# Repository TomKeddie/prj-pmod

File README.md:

# prj-pmod

A collection of BSD licensed hardware designs for the PMOD form factor.

MIT licensed - see https://github.com/TomKeddie/prj-pmod/blob/master/LICENSE

## tom-prj-pmod

This is a PMOD module with a SAMD21 cpu on it to make it easy to add an ARM cpu to an fpga project.

Hardware : https://github.com/TomKeddie/prj-pmod/tree/master/hardware/pmod-samd21

Bootloader : https://github.com/TomKeddie/prj-pmod/tree/master/software/pmod-samd21

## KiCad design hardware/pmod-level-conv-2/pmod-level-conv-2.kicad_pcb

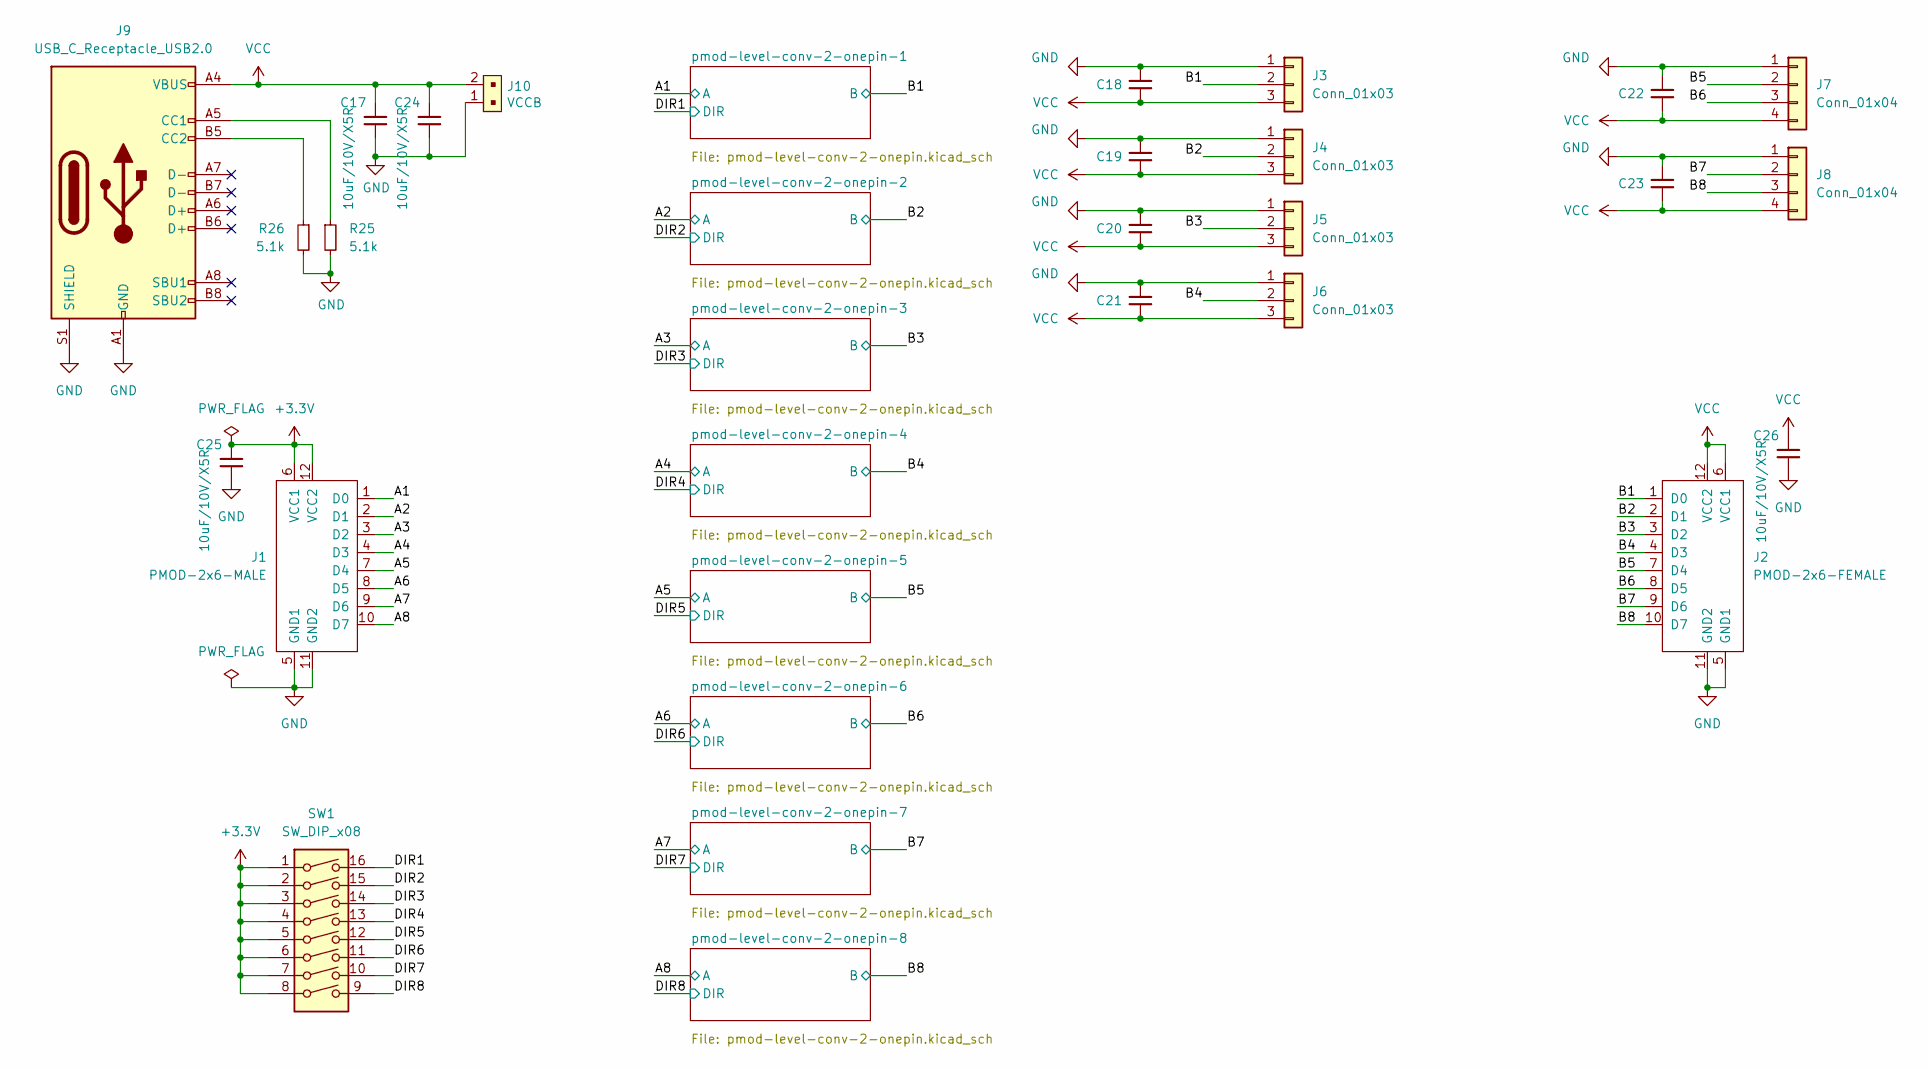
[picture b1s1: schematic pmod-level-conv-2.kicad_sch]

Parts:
C17, C18, C19, C20, C21, C22, C23, C24, C25, C26: 10uF/10V/X5R; C_0603_1608Metric; MFGPN CL10A106KP8NNNC; LCSC C19702
J1: PMOD-2x6-MALE; PMOD_2X6_PTH_RA_PLUG; LCSC DNP
J2: PMOD-2x6-FEMALE; PMOD_2X6_PTH_RA_SOCKET; LCSC DNP
J3, J4, J5, J6: Conn_01x03; CONN_ZH_3P_HORIZ_C722679; LCSC C722679
J7, J8: Conn_01x04; CONN_ZH_4P_HORIZ_C5248024; LCSC C5248024
J9: USB_C_Receptacle_USB2.0; USB_C_Receptacle_LCSC_C165948; LCSC C165948
J10: VCCB; CONN_ZH_2P_HORIZ_C265329; LCSC C265329
R25, R26: 5.1k; R_0402_1005Metric; MFGPN 0402WGF5101TCE; LCSC C25905
SW1: SW_DIP_x08; DIP-16_W7.62mm_Socket_LongPads; LCSC DNP

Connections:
+3.3V: C25.1, J1.6 (VCC1), J1.12 (VCC2), SW1.1, SW1.2, SW1.3, SW1.4, SW1.5, SW1.6, SW1.7, SW1.8; also elsewhere on the board
/A1: J1.1 (D0); also elsewhere on the board
/A2: J1.2 (D1); also elsewhere on the board
/A3: J1.3 (D2); also elsewhere on the board
/A4: J1.4 (D3); also elsewhere on the board
/A5: J1.7 (D4); also elsewhere on the board
/A6: J1.8 (D5); also elsewhere on the board
/A7: J1.9 (D6); also elsewhere on the board
/A8: J1.10 (D7); also elsewhere on the board
/B1: J2.1 (D0), J3.2; also elsewhere on the board
/B2: J2.2 (D1), J4.2; also elsewhere on the board
/B3: J2.3 (D2), J5.2; also elsewhere on the board
/B4: J2.4 (D3), J6.2; also elsewhere on the board
/B5: J2.7 (D4), J7.2; also elsewhere on the board
/B6: J2.8 (D5), J7.3; also elsewhere on the board
/B7: J2.9 (D6), J8.2; also elsewhere on the board
/B8: J2.10 (D7), J8.3; also elsewhere on the board
/DIR1: SW1.16; also elsewhere on the board
/DIR2: SW1.15; also elsewhere on the board
/DIR3: SW1.14; also elsewhere on the board
/DIR4: SW1.13; also elsewhere on the board
/DIR5: SW1.12; also elsewhere on the board
/DIR6: SW1.11; also elsewhere on the board
/DIR7: SW1.10; also elsewhere on the board
/DIR8: SW1.9; also elsewhere on the board
GND: C17.2, C18.1, C19.1, C20.1, C21.1, C22.1, C23.1, C24.2, C25.2, C26.2, J1.5 (GND1), J1.11 (GND2), J2.5 (GND1), J2.11 (GND2), J3.1, J4.1, J5.1, J6.1, J7.1, J8.1, J9.A1 (GND), J9.A12 (GND), J9.B1 (GND), J9.B12 (GND), J9.S1 (SHIELD), J10.1, R25.2, R26.2; also elsewhere on the board
unnamed: J9.A5 (CC1), R25.1
unnamed: J9.B5 (CC2), R26.1
VCC: C17.1, C18.2, C19.2, C20.2, C21.2, C22.2, C23.2, C24.1, C26.1, J2.6 (VCC1), J2.12 (VCC2), J3.3, J4.3, J5.3, J6.3, J7.4, J8.4, J9.A4 (VBUS), J9.A9 (VBUS), J9.B4 (VBUS), J9.B9 (VBUS), J10.2; also elsewhere on the board

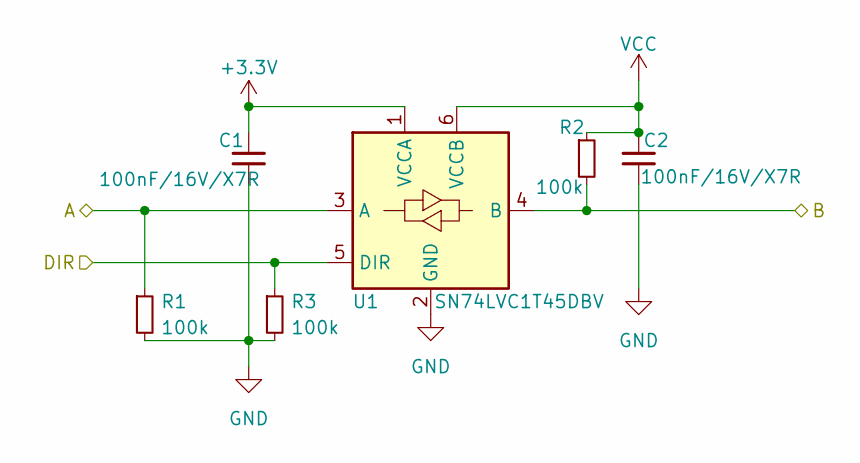
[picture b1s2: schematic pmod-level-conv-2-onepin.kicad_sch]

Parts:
C1, C2: 100nF/16V/X7R; C_0402_1005Metric; MFGPN CL05B104KO5NNNC; LCSC C1525
R1, R2, R3: 100k; R_0402_1005Metric; MFGPN 0402WGF1003TCE; LCSC C25741
U1: SN74LVC1T45DBV; SOT-23-6; LCSC C7843

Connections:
+3.3V: C1.1, U1.1 (VCCA); also elsewhere on the board
/A1: R1.1, U1.3 (A); also elsewhere on the board
/B1: R2.2, U1.4 (B); also elsewhere on the board
/DIR1: R3.1, U1.5 (DIR); also elsewhere on the board
GND: C1.2, C2.2, R1.2, R3.2, U1.2 (GND); also elsewhere on the board
VCC: C2.1, R2.1, U1.6 (VCCB); also elsewhere on the board

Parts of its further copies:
C3, C4, C5, C6, C7, C8, C9, C10, C11, C12, C13, C14, C15, C16: 100nF/16V/X7R; C_0402_1005Metric; MFGPN CL05B104KO5NNNC; LCSC C1525
R4, R5, R6, R7, R8, R9, R10, R11, R12, R13, R14, R15, R16, R17, R18, R19, R20, R21, R22, R23, R24: 100k; R_0402_1005Metric; MFGPN 0402WGF1003TCE; LCSC C25741
U2, U3, U4, U5, U6, U7, U8: SN74LVC1T45DBV; SOT-23-6; LCSC C7843

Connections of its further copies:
+3.3V: C3.1, C5.1, C7.1, C9.1, C11.1, C13.1, C15.1, U2.1 (VCCA), U3.1 (VCCA), U4.1 (VCCA), U5.1 (VCCA), U6.1 (VCCA), U7.1 (VCCA), U8.1 (VCCA); also elsewhere on the board
/A2: R5.1, U2.3 (A); also elsewhere on the board
/A3: R8.1, U3.3 (A); also elsewhere on the board
/A4: R11.1, U4.3 (A); also elsewhere on the board
/A5: R14.1, U5.3 (A); also elsewhere on the board
/A6: R17.1, U6.3 (A); also elsewhere on the board
/A7: R20.1, U7.3 (A); also elsewhere on the board
/A8: R23.1, U8.3 (A); also elsewhere on the board
/B2: R4.2, U2.4 (B); also elsewhere on the board
/B3: R7.2, U3.4 (B); also elsewhere on the board
/B4: R10.2, U4.4 (B); also elsewhere on the board
/B5: R13.2, U5.4 (B); also elsewhere on the board
/B6: R16.2, U6.4 (B); also elsewhere on the board
/B7: R19.2, U7.4 (B); also elsewhere on the board
/B8: R22.2, U8.4 (B); also elsewhere on the board
/DIR2: R6.1, U2.5 (DIR); also elsewhere on the board
/DIR3: R9.1, U3.5 (DIR); also elsewhere on the board
/DIR4: R12.1, U4.5 (DIR); also elsewhere on the board
/DIR5: R15.1, U5.5 (DIR); also elsewhere on the board
/DIR6: R18.1, U6.5 (DIR); also elsewhere on the board
/DIR7: R21.1, U7.5 (DIR); also elsewhere on the board
/DIR8: R24.1, U8.5 (DIR); also elsewhere on the board
GND: C3.2, C4.2, C5.2, C6.2, C7.2, C8.2, C9.2, C10.2, C11.2, C12.2, C13.2, C14.2, C15.2, C16.2, R5.2, R6.2, R8.2, R9.2, R11.2, R12.2, R14.2, R15.2, R17.2, R18.2, R20.2, R21.2, R23.2, R24.2, U2.2 (GND), U3.2 (GND), U4.2 (GND), U5.2 (GND), U6.2 (GND), U7.2 (GND), U8.2 (GND); also elsewhere on the board
VCC: C4.1, C6.1, C8.1, C10.1, C12.1, C14.1, C16.1, R4.1, R7.1, R10.1, R13.1, R16.1, R19.1, R22.1, U2.6 (VCCB), U3.6 (VCCB), U4.6 (VCCB), U5.6 (VCCB), U6.6 (VCCB), U7.6 (VCCB), U8.6 (VCCB); also elsewhere on the board

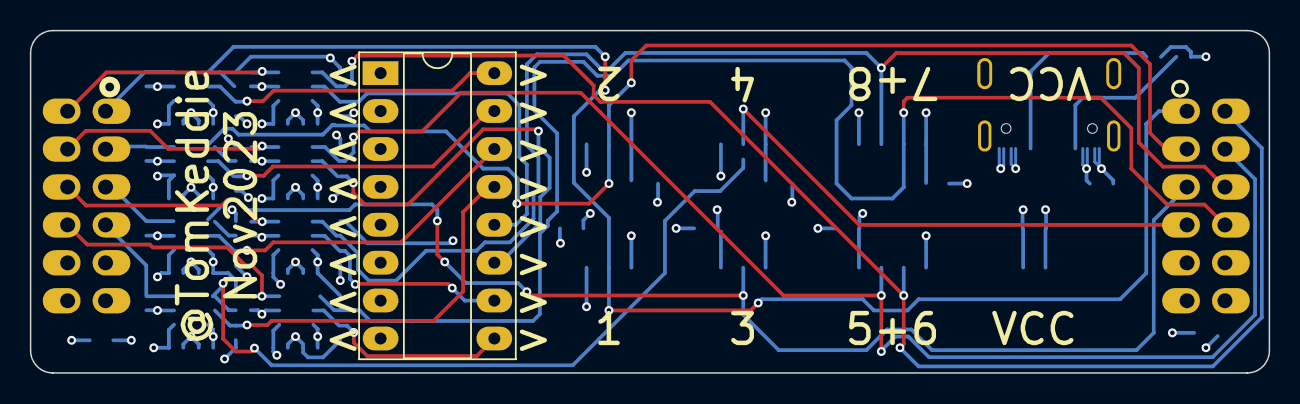
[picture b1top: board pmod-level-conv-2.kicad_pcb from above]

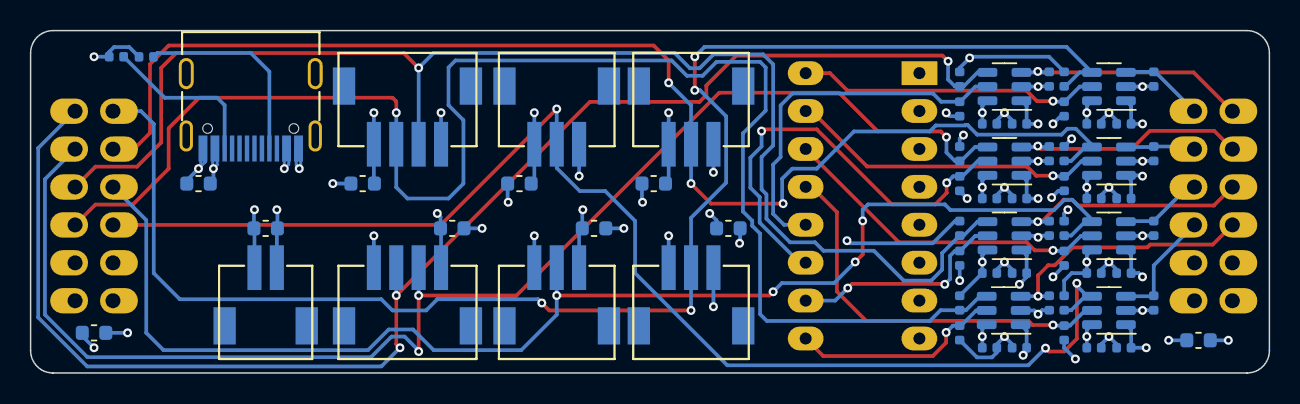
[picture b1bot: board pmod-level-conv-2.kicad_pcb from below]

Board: 4 copper layers, 83.0 x 22.9 mm, 71 parts (68 on the bottom side), 29 nets.

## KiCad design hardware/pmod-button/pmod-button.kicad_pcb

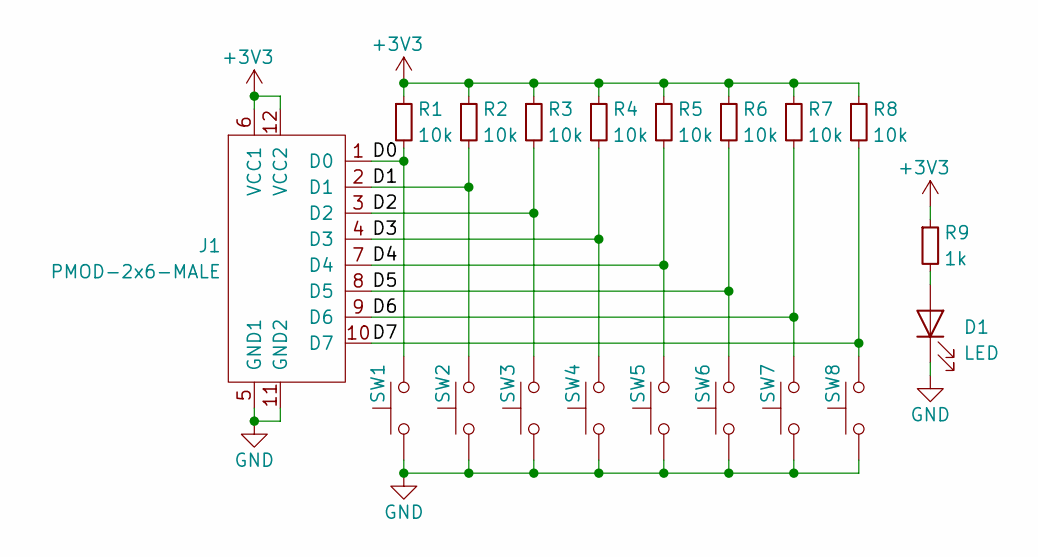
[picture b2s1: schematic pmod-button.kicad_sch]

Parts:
D1: LED; LED_0805_2012Metric_Pad1.15x1.40mm_HandSolder
J1: PMOD-2x6-MALE; PMOD_2X6_PTH_RA_PLUG
R1, R2, R3, R4, R5, R6, R7, R8: 10k; C_0805_2012Metric_Pad1.15x1.40mm_HandSolder
R9: 1k; C_0805_2012Metric_Pad1.15x1.40mm_HandSolder
SW1, SW2, SW3, SW4, SW5, SW6, SW7, SW8: Switch_SW_Push; SW_Push_1P1T_NO_CK_PTS125Sx43PSMTR

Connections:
+3V3: J1.6 (VCC1), J1.12 (VCC2), R1.1, R2.1, R3.1, R4.1, R5.1, R6.1, R7.1, R8.1, R9.1
/D0: J1.1 (D0), R1.2, SW1.2
/D1: J1.2 (D1), R2.2, SW2.2
/D2: J1.3 (D2), R3.2, SW3.2
/D3: J1.4 (D3), R4.2, SW4.2
/D4: J1.7 (D4), R5.2, SW5.2
/D5: J1.8 (D5), R6.2, SW6.2
/D6: J1.9 (D6), R7.2, SW7.2
/D7: J1.10 (D7), R8.2, SW8.2
GND: D1.1 (K), J1.5 (GND1), J1.11 (GND2), SW1.1, SW2.1, SW3.1, SW4.1, SW5.1, SW6.1, SW7.1, SW8.1
unnamed: D1.2 (A), R9.2

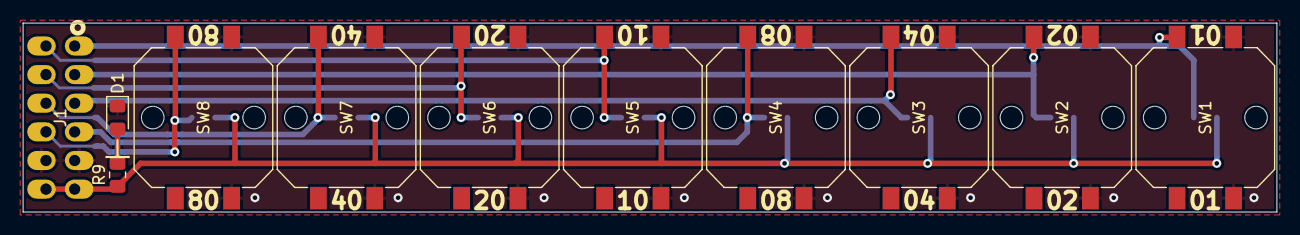
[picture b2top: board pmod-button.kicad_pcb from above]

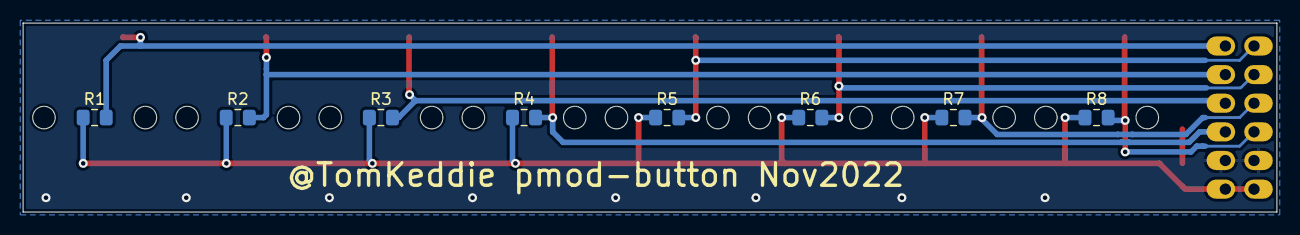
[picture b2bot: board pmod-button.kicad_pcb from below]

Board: 2 copper layers, 111.3 x 16.8 mm, 19 parts (8 on the bottom side), 11 nets.

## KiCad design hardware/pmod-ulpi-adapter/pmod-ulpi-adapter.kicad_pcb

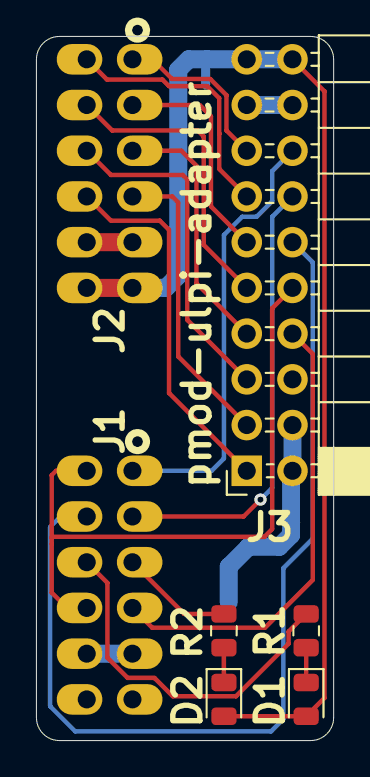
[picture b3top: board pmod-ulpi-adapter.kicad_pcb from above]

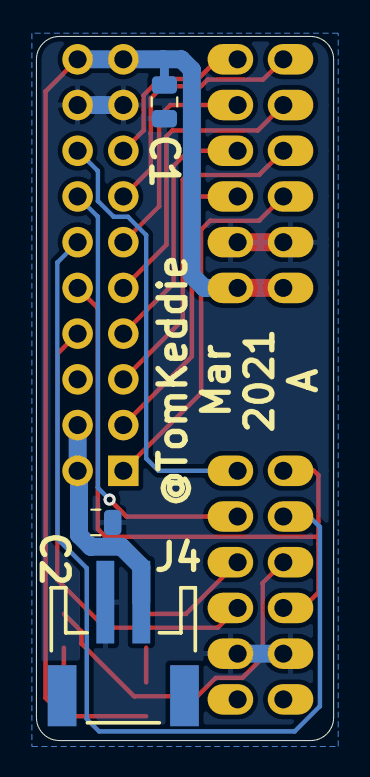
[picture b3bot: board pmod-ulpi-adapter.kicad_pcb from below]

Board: 2 copper layers, 16.5 x 39.1 mm, 10 parts (3 on the bottom side), 20 nets.

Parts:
C1, C2: 10uF/10V; C_0805_2012Metric
D1, D2: LED; LED_0805_2012Metric
J1, J2: PMOD-2x6-MALE; PMOD_2X6_PTH_RA_PLUG
J3: ULPI; PinSocket_2x10_P2.54mm_Horizontal
J4: Conn_01x02; JST-2-SMD
R1, R2: 1k; R_0805_2012Metric

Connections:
+3V3: C1.2, D1.2, D2.2, J2.6, J2.12, J3.19, J3.20
+5V: C2.2, J3.2, J3.4, J4.1
/BLUE: J1.9, R1.2
/CLKOUT: J1.7, J1.10, J3.10
/DATA0: J2.10, J3.1
/DATA1: J2.4, J3.3
/DATA2: J2.9, J3.5
/DATA3: J2.3, J3.7
/DATA4: J2.8, J3.9
/DATA5: J2.2, J3.11
/DATA6: J2.7, J3.13
/DATA7: J2.1, J3.15
/DIR: J1.8, J3.12
/NXT: J1.2, J3.14
/RESET: J1.4, J3.8
/STP: J1.1, J3.16
/YELLOW: J1.3, R2.1
GND: C1.1, C2.1, J1.5, J1.11, J2.5, J2.11, J3.17, J3.18, J4.2
unnamed: D1.1, R1.1
unnamed: D2.1, R2.2

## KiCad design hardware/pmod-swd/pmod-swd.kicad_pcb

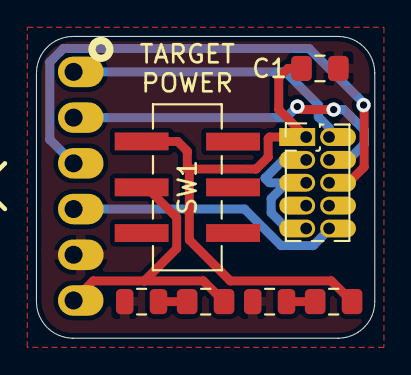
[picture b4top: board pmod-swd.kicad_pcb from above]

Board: 2 copper layers, 18.8 x 16.8 mm, 8 parts (0 on the bottom side), 9 nets.

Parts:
C1: 10uF/6.3V; C_0805_2012Metric_Pad1.15x1.40mm_HandSolder
D1, D2: LED; C_0805_2012Metric_Pad1.15x1.40mm_HandSolder
J1: PMOD; PMOD_1X6_PTH_RA_PLUG
J2: SWD; PinHeader_2x05_P1.27mm_Vertical
R1, R2: 1k; R_0805_2012Metric
SW1: SW_DPDT_x2; SW_DPDT_SMD

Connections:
!RESET: J1.4, J2.10
+3V3: D1.2, J1.6, SW1.2
GND: C1.2, J1.5, J2.3, J2.5, J2.9, R1.2, R2.2
unnamed: D1.1, R1.1
unnamed: D2.1, R2.1
SWDCLK: J1.2, J2.4
SWDIO: J1.1, J2.2
SWO: J1.3, J2.6
VCC: C1.1, D2.2, J2.1, SW1.3

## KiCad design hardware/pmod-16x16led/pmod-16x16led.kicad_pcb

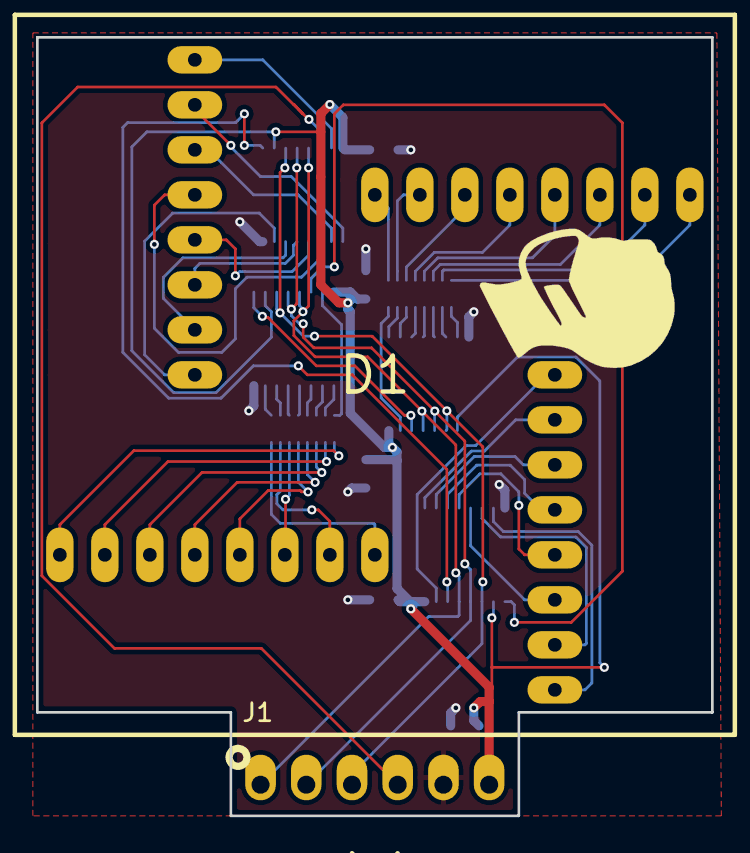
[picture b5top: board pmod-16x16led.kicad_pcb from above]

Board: 2 copper layers, 37.5 x 43.2 mm, 13 parts (0 on the bottom side), 57 nets.

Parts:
C1: 10uF/6.3V; C_0603_1608Metric
C2, C3, C4, C5: 0.1uF/6.3V; C_0603_1608Metric
D1: SLD161616DRA2B
J1: Conn_01x06; PMOD_1X6_PTH_RA_PLUG
RP1, RP2: 330R; R_PACK8_CAT16J8
U1, U2, U3, U4: 74HC595; SSOP-16_3.9x4.9mm_P0.635mm

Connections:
+3V3: C1.1, C2.1, C3.1, C4.1, C5.1, J1.6, U1.10, U1.16, U2.10, U2.16, U3.10, U3.16, U4.10, U4.16
/!OE: J1.1, U1.13, U2.13, U3.13, U4.13
/A1: D1.25, U1.15
/A2: D1.26, U1.1
/A3: D1.27, U1.2
/A4: D1.28, U1.3
/A5: D1.29, U1.4
/A6: D1.30, U1.5
/A7: D1.31, U1.6
/A8: D1.32, U1.7
/A9: D1.16, U2.15
/A10: D1.15, U2.1
/A11: D1.14, U2.2
/A12: D1.13, U2.3
/A13: D1.12, U2.4
/A14: D1.11, U2.5
/A15: D1.10, U2.6
/A16: D1.9, U2.7
/C1: D1.1, RP1.9
/C2: D1.2, RP1.10
/C3: D1.3, RP1.11
/C4: D1.4, RP1.12
/C5: D1.5, RP1.13
/C6: D1.6, RP1.14
/C7: D1.7, RP1.15
/C8: D1.8, RP1.16
/C9: D1.24, RP2.9
/C10: D1.23, RP2.10
/C11: D1.22, RP2.11
/C12: D1.21, RP2.12
/C13: D1.20, RP2.13
/C14: D1.19, RP2.14
/C15: D1.18, RP2.15
/C16: D1.17, RP2.16
/CLK: J1.3, U1.11, U2.11, U3.11, U4.11
/DATA: J1.4, U1.14
/DATA-A8: U1.9, U2.14
/DATA-A16: U2.9, U3.14
/DATA-C8: U3.9, U4.14
/RCLK: J1.2, U1.12, U2.12, U3.12, U4.12
GND: C1.2, C2.2, C3.2, C4.2, C5.2, J1.5, U1.8, U2.8, U3.8, U4.8
unnamed: RP1.1, U3.7
unnamed: RP1.2, U3.6
unnamed: RP1.3, U3.5
unnamed: RP1.4, U3.4
unnamed: RP1.5, U3.3
unnamed: RP1.6, U3.2
unnamed: RP1.7, U3.1
unnamed: RP1.8, U3.15
unnamed: RP2.1, U4.7
unnamed: RP2.2, U4.6
unnamed: RP2.3, U4.5
unnamed: RP2.4, U4.4
unnamed: RP2.5, U4.3
unnamed: RP2.6, U4.2
unnamed: RP2.7, U4.1
unnamed: RP2.8, U4.15

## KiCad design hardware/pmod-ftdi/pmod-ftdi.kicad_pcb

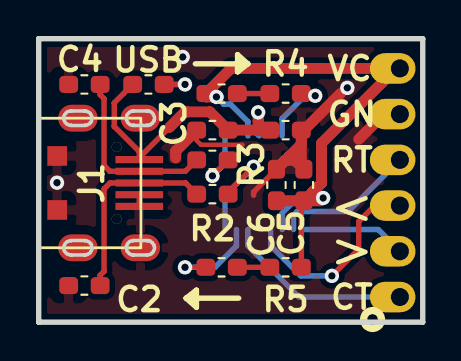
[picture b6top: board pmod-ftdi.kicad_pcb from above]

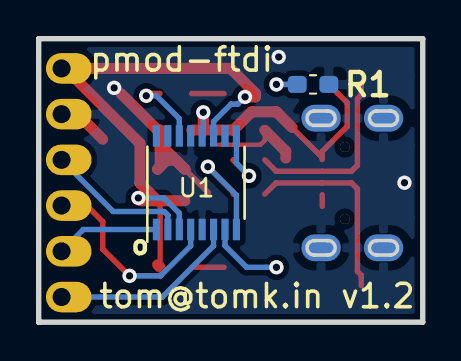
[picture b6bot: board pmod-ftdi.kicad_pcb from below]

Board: 2 copper layers, 21.3 x 15.7 mm, 17 parts (2 on the bottom side), 16 nets.

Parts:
C1, C5: 4.7uF; C_0603_1608Metric_Pad1.05x0.95mm_HandSolder
C2, C4: 47pF; C_0603_1608Metric_Pad1.05x0.95mm_HandSolder
C3, C6: 0.1uF; C_0603_1608Metric_Pad1.05x0.95mm_HandSolder
D1: VBUS; R_0603_1608Metric_Pad1.05x0.95mm_HandSolder
D2: TX; R_0603_1608Metric_Pad1.05x0.95mm_HandSolder
D3: RX; R_0603_1608Metric_Pad1.05x0.95mm_HandSolder
J1: USB_B_Micro; USB_MICRO_TAOBAO_SMD_PTH
J2: PMOD-1x6-MALE; PMOD_1X6_PTH_RA_PLUG
R1, R4, R5: 1k; R_0603_1608Metric_Pad1.05x0.95mm_HandSolder
R2, R3: 27R; R_0603_1608Metric_Pad1.05x0.95mm_HandSolder
U1: FT230XS-R; SSOP-16_3.9x4.9mm_P0.635mm

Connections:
/CBUS1: R4.1, U1.14
/CBUS2: D3.1, U1.7
/CTS: J2.1, U1.6
/D_N: R3.2, U1.9
/D_P: R2.1, U1.8
/RTS: J2.4, U1.2
/RXD: J2.3, U1.4
/RXLED: D3.2, R5.1
/TXD: J2.2, U1.1
/TXLED: D2.1, R4.2
/UD_N: C4.1, J1.2, R3.1
/UD_P: C2.1, J1.3, R2.2
/VBUSLED: D1.1, R1.2
GND: C1.2, C2.2, C3.2, C4.2, C5.2, C6.2, J1.4, J1.5, J1.6, J2.5, R1.1, U1.5, U1.13
VBUS: C1.1, C3.1, D1.2, J1.1, U1.12
VCCIO: C5.1, C6.1, D2.2, J2.6, R5.2, U1.3, U1.11

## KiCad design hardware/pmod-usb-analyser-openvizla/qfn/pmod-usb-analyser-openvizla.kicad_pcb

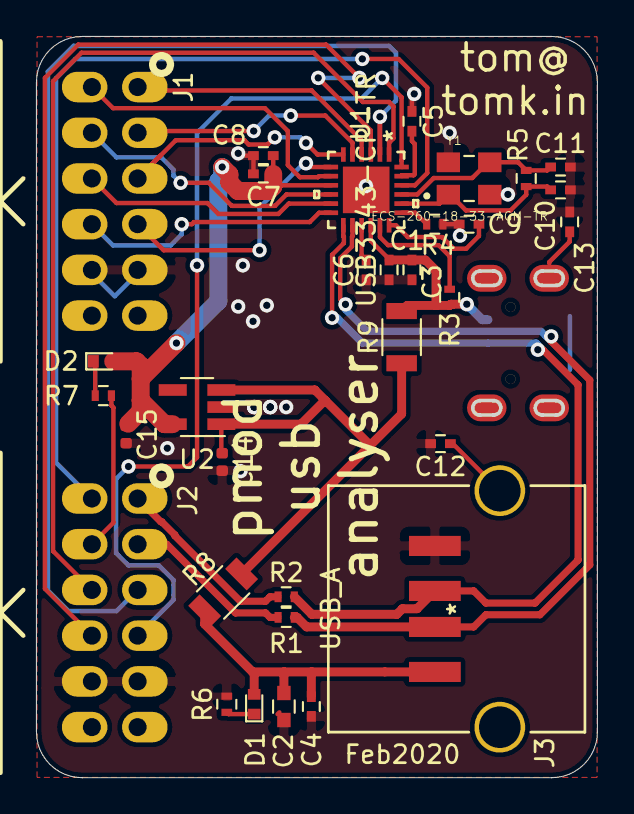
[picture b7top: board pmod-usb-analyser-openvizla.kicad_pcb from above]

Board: 2 copper layers, 31.0 x 41.0 mm, 33 parts (1 on the bottom side), 34 nets.

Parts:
C1, C3, C7, C9: 0.1uF; C_0402
C2: 10uF; C_0603
C4, C5, C6, C8: 1uF; C_0402
C10, C11: 18pF; C_0402
C12, C13: 0.1uF/6.3V; C_0402
C14, C15: 1uF; C_0402_1005Metric
D1, D2: LED; LED_0402
J1, J2: PMOD-2x6-MALE; PMOD_2X6_PTH_RA_PLUG
J3: USB_A; 87583-2010BLF
J4: USB_B_Micro; USB_MICRO_TAOBAO_SMD_PTH
R1, R2: 1k; R_0402
R3: 10k; R_0402
R4: 8k06/1%; R_0402
R5: 1M; R_0402
R6: 1K; R_0402
R7: 330R; R_0402
R8, R9: R; R_1206
U1: USB3343-CP-TR
U2: AP2112K-3.3; SOT-23-5_HandSoldering
Y1: ECS-260-18-33-AGM-TR; XTAL_ECS-260-18-33-AGM-TR

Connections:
+3V3: C7.1, C8.1, C15.1, D2.2, U1.9, U2.5
/CLKOUT: J2.3, U1.2
/DATA0: J1.1, U1.4
/DATA1: J1.2, U1.5
/DATA2: J1.3, U1.6
/DATA3: J1.4, U1.7
/DATA4: J1.7, U1.8
/DATA5: J1.8, U1.10
/DATA6: J1.9, U1.11
/DATA7: J1.10, U1.12
/DIR: J2.9, U1.1
/ID: C9.1, U1.18
/J3_SHIELD: C12.1, J3.5
/J4_SHIELD: C13.1, J4.6
/NXT: J2.10, U1.3
/RBIAS: R4.2, U1.19
/RESETB: J2.7, U1.22
/STP: J2.4, U1.24
/USB_TAP_DP: J2.1, R2.1
/USER_LED: J2.8, R7.2
/VBUS: C2.1, C4.1, D1.2, J3.1, R8.1
/VBUS_SENSE: R3.1, U1.17
/VDD18: C5.1, U1.23
/VDD33: C6.1, U1.15
/X0: C10.1, R5.1, U1.20, Y1.1
/XI: C11.1, R5.2, U1.21, Y1.3
GND: C1.2, C2.2, C3.2, C4.2, C5.2, C6.2, C7.2, C8.2, C9.2, C10.2, C11.2, C12.2, C13.2, C14.2, C15.2, J1.5, J1.11, J2.5, J2.11, J3.4, J4.5, R4.1, R6.2, U1.25, U2.2, Y1.2, Y1.4
unnamed: D1.1, R6.1
unnamed: D2.1, R7.1
unnamed: J2.2, R1.1
USB_DN: J3.2, J4.2, R1.2, U1.14
USB_DP: J3.3, J4.3, R2.2, U1.13
VBUS1: C14.1, R8.2, R9.1, U2.1, U2.3
VBUS2: C1.1, C3.1, J4.1, R3.2, R9.2, U1.16

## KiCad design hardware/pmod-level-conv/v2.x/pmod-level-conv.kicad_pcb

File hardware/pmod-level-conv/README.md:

# PMOD Level Converter

Converts up in voltage only (within specs of TXB0108).  Would be trivial to flip/reverse the connectors and hack the board to convert down.

Status : TSSOP v1.0 tested and working. TSOP v1.2 tested, changed only side of header pads. VQFN v1.3 untested.

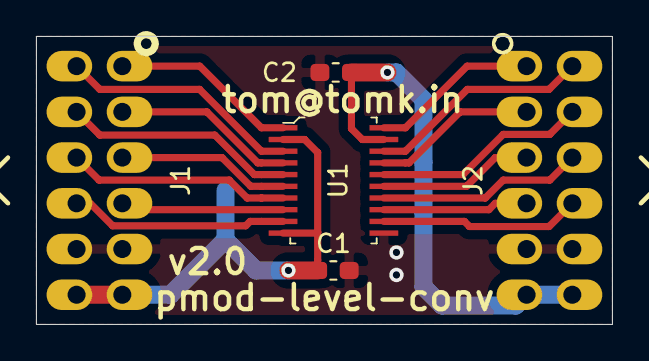
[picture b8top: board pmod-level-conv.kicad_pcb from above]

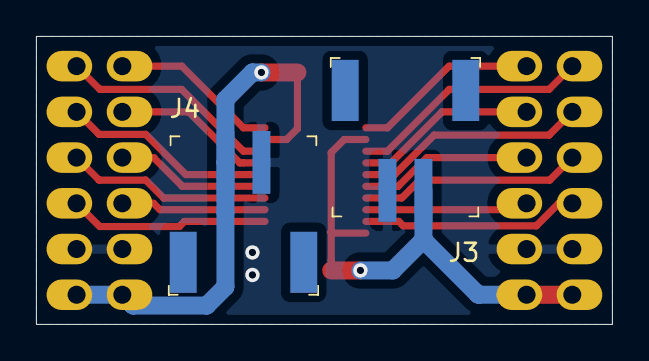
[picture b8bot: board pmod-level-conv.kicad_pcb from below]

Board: 2 copper layers, 32.0 x 16.0 mm, 7 parts (2 on the bottom side), 19 nets.

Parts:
C1, C2: 0.1uF/10V; C_0603_1608Metric_Pad1.05x0.95mm_HandSolder
J1: PMOD-2x6-MALE; PMOD_2X6_PTH_RA_PLUG
J2: PMOD-2x6-FEMALE; PMOD_2X6_PTH_RA_SOCKET
J3: VCCA; PinHeader_2x1mm_P2mm_SMD_RA
J4: VCCB; PinHeader_2x1mm_P2mm_SMD_RA
U1: TXB0108PWR; TSSOP-20_W4.4mm

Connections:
/A1: J1.1, U1.1
/A2: J1.7, U1.3
/A3: J1.2, U1.4
/A4: J1.8, U1.5
/A5: J1.3, U1.6
/A6: J1.9, U1.7
/A7: J1.4, U1.8
/A8: J1.10, U1.9
/B1: J2.1, U1.20
/B2: J2.7, U1.18
/B3: J2.2, U1.17
/B4: J2.8, U1.16
/B5: J2.3, U1.15
/B6: J2.9, U1.14
/B7: J2.4, U1.13
/B8: J2.10, U1.12
/VCCA: C1.1, J1.6, J1.12, J3.2, U1.2, U1.10
/VCCB: C2.1, J2.6, J2.12, J4.2, U1.19
GND: C1.2, C2.2, J1.5, J1.11, J2.5, J2.11, J3.1, J4.1, U1.11

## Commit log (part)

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2018-05-27 PMOD USB RAW for tinyfpga bootloader - rev 1.0 as sent to oshpark
2018-06-20 Added README
2018-06-20 Add oshpark link
2018-06-20 Added images of USB PMOD
2018-06-20 Added BOM for usb pmod
2018-06-20 Updated usb README to add octopart
2018-06-20 Add image for usb raw pmod
2018-06-20 Add image to USB readme
2018-06-20 Update README to show image
2018-06-20 Fix typo in README
2018-06-24 pmod level converter added (v1.0 as sent to oshpark)
2018-07-26 Update level conv pcb to rev 1.1 - fix smd pad sizes for pmod connectors
2018-07-27 Eight LED PMOD as submitted to OSH Park
2018-08-06 Added APA102 PMOD board
2018-08-06 APA102 PMD as submitted to Oshpark (minor silk fixups)
2018-08-13 pmod-level-conv : fixed NC OE
2018-10-28 Added VQFN version of pmod level converter
2018-10-28 Added eagle samd5x5 schematic
2018-10-30 First pass at kicad schematic for samd21 pmod
2018-10-31 Add kicad backups to gitignore
2018-10-31 First pass at routing of samd21 pmod, power yet to be done
2018-10-31 PCB fully routed with DRC errors ignored - oshpark doesn't like the slots in the usb connector - need to check FET pinout
2018-11-26 pcb as submitted to oshpark
2018-11-26 Added pmod-samd21 openocd config
2018-11-26 Add samd bootloader from Arduino for pmod-samd21
2018-11-26 Add sam_ba build for pmod-samd21 with led on B23
2018-11-26 Fix path to sam_ba binary
2018-12-05 pmod-samd21 : Fixed edge cuts for panelisation with plated slots
2018-12-07 pmod-samd21 - added missing usb C resistors - generated gerbers relative to aux origin
2018-12-07 pmod-samd21 : rename to create usb-c variant
2018-12-07 pmod-samd : clone usbc variant to make microusb variant
2018-12-09 SAMD21 PMOD microusb version
2018-12-09 pmod-samd21 : add missing gerbers for usbu variant
2018-12-09 pmod-samd21 : Move usbu gerbers to separate folder
2018-12-31 Updated led pmod
2019-01-16 Added pcb for micro usb samd21 pmod
2019-01-16 pmod-samd21 : routed and ready for fab
2019-03-20 Add ibom for pmod-samd21-usbu
2019-03-20 Create LICENSE
2019-03-20 pmod-samd21-usbu-pth : as sent to fab
2019-03-20 gerber-usbu-pth : add missing drill file
2019-03-20 Update README.md
    Add Arduino digital and analog pin numbers
2019-03-20 Update README.md
    Add arduino aliases
2019-03-21 Update README.md
    Add notes on power supply.
2019-04-25 pmod-samd21 : added prj-fpga submodule
2019-04-25 pmod-samd21 : changes for seeed studio opl fabrication
2019-04-25 Add PTC pin details to README.
2019-04-26 Update README.md
    Add pin details for SPI and PTC
2019-04-26 pmod-samd21: update to use pidcodes PID, fix manufacturer name (use BOARD_ID=pmod_samd21 NAME=pmod_samd21 make)
2019-04-26 pmod-samd21: first pass at hdl example for pmod-samd21-midi
2019-04-26 pmod-samd21 : minor updates
2019-05-05 pmod-usb-analyser-openvizla : first pass at usb analyser pmod
2019-05-05 pmod-usb-analyser-openvizla : remove refs from silk
2019-08-28 Add pmod-sao : shitty addon pmod
2019-09-02 Added pmod-fan5702 as submitted to oshpark
2019-09-02 Updated submodule tom-kicad
2019-09-08 Move pmod-samd21-usbu-pth to separate project
2019-09-08 Fix IO assignments on PMOD so both i2c and spi work
2019-09-08 Add kicad specific gitignore, move pmod-samd21-usbu-pth to subdir
2019-09-09 pmod-samd21-usbu-pth : fix pin assignments to make i2c and spi viable
2019-09-10 pmod-samd21: routed pth version with spi/i2c compatibile addressing
2019-09-11 pmod-samd21: Fix PCB rev in silk
2019-09-26 pmod-samd21-usbc: move files to separate directory
2019-10-06 pmod-sao : added images
2019-10-06 pmod-level-conv : add doco
2019-10-16 pmod-usb-analyser-openvizla: add missing files, fix library references
2019-10-16 pmod-usb-analyser-openvizla: move old pcb to qfn suibdirectory ready to create BGA version
2019-10-19 pmod-usb-analyser-openvizla: add schematic image
2019-11-09 pmod-level-conv: restructure files
2019-11-09 pmod-level-conv: add v2.x
2019-12-13 pmod-ftdi : v1.0
2020-01-11 pmod-ftdi: rev 1.1 - fix ft230xs package
2020-01-11 pmod-ftdi: switch to correct symbol for FT230XS
2020-02-05 pmod-usb-analyser: feedback from ktempkin - move VBAT to 5V - moved 3.3V to LDO
2020-02-05 Submodule update
2020-02-05 pmod-ftdi : as built
2020-02-05 update gitignore
2020-04-07 pmod-16x16led: add 16x16 led matrix pmod
2020-04-08 pmod-16x16led: Apr2020 version as submitted to oshpark
2020-11-22 hardware: update tom-kicad submodule to latest
2020-11-22 pmod-swd: Nov2020 release
2020-11-27 Update tom-kicad submodule
2020-12-08 pmod-rgb-led: first steps of an RGB led matrix
2020-12-08 pmod-rgb-led: add bus name to fix erc errors
2020-12-08 pmod-rgb-led: update tom-kicad to use local copy
2020-12-08 Add missed files
2021-03-12 pmod-ulpi-adapter: adapter to connect cheap ulpi board to pmod
2021-03-12 pmod-ulpi-adapter: Mar2021A release, swapped pmod connectors for more clock option
2022-11-21 hardware/pmod-button: new design
2023-11-25 pmod-level-conv-2: new design

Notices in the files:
parts and their libraries:
Copyright 2016 Accelerated Designs. All rights reserved.
